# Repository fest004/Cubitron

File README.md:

```
   ▄█   ▄█▄ ███    █▄  ▀█████████▄     ▄████████ ███▄▄▄▄   
  ███ ▄███▀ ███    ███   ███    ███   ███    ███ ███▀▀▀██▄ 
  ███▐██▀   ███    ███   ███    ███   ███    █▀  ███   ███ 
 ▄█████▀    ███    ███  ▄███▄▄▄██▀   ▄███▄▄▄     ███   ███ 
▀▀█████▄    ███    ███ ▀▀███▀▀▀██▄  ▀▀███▀▀▀     ███   ███ 
  ███▐██▄   ███    ███   ███    ██▄   ███    █▄  ███   ███ 
  ███ ▀███▄ ███    ███   ███    ███   ███    ███ ███   ███ 
  ███   ▀█▀ ████████▀  ▄█████████▀    ██████████  ▀█   █▀  
  ▀                                                        
```
#### You can read about it here: [Link to documentation](https://fest004.github.io/Cubitron/)

#### Folder structure

```
.
├── docs             # Documents (datasheets, references, documentation)
├── hardware         # Hardware design files (CAD)
├── software         # Software files (source files, build files and binaries)
├── LICENSE
└── README.md
```

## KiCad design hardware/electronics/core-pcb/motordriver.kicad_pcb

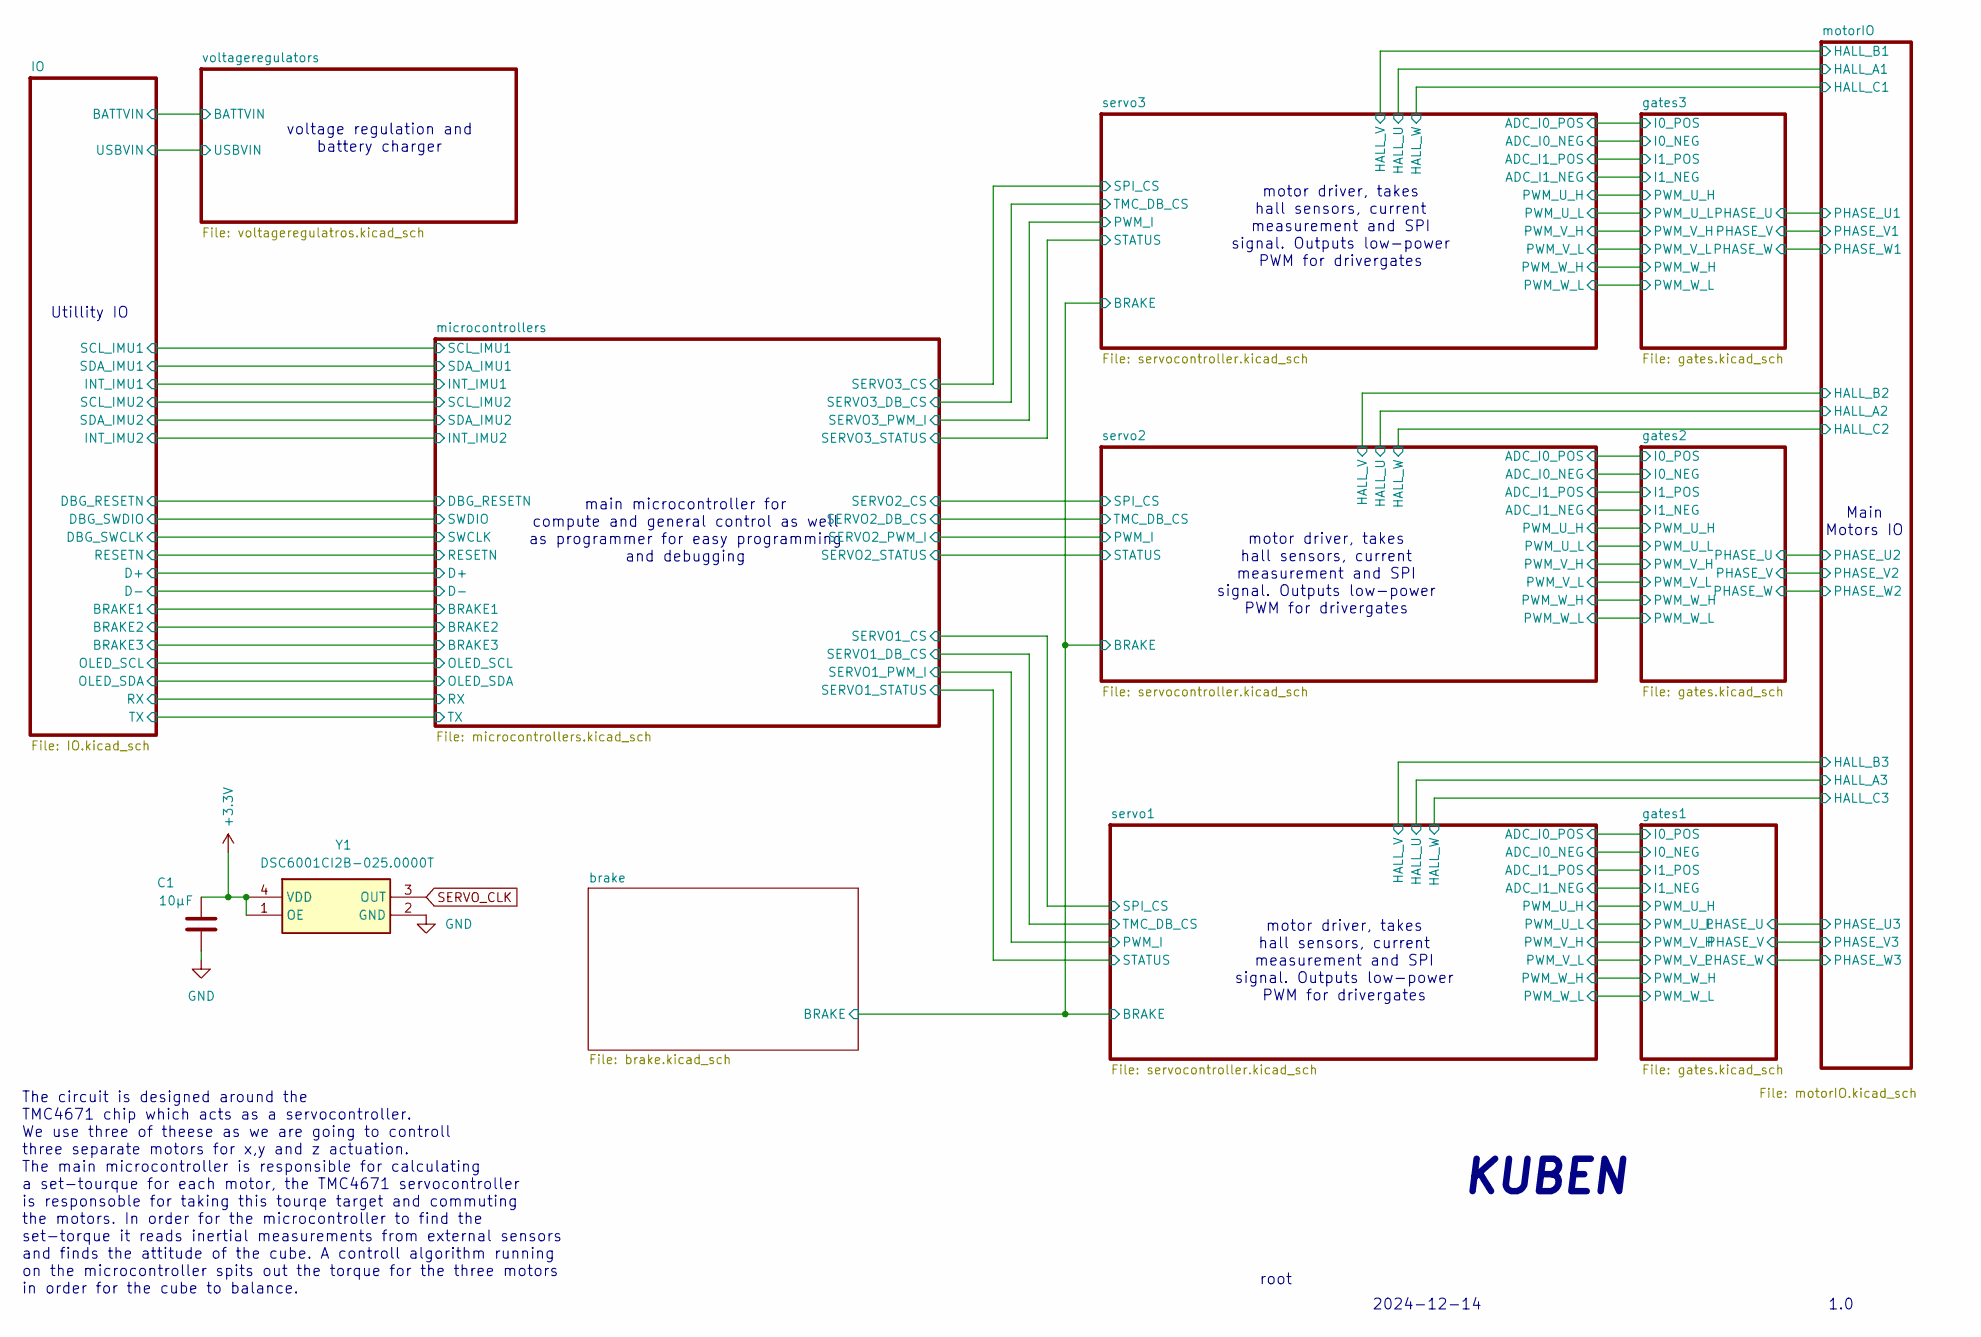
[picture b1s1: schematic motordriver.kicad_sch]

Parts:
C1: 10µF; C_0603_1608Metric
Y1: DSC6001CI2B-025.0000T; DSC6001CI2B0250000T; Mouser Part Number 579-1CI2B-025.0000T

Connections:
+3.3V: C1.1, Y1.1 (OE), Y1.4 (VDD); also elsewhere on the board
SERVO_CLK: Y1.3 (OUT); also elsewhere on the board

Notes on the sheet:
1.0
voltage regulation and battery charger
motor driver, takes hall sensors, current measurement and SPI signal. Outputs low-power PWM for drivergates
root
Main Motors IO
KUBEN
2024-12-14
main microcontroller for compute and general control as well as programmer for easy programming and debugging
Utillity IO
The circuit is designed around the TMC4671 chip which acts as a servocontroller. We use three of theese as we are going to controll three separate motors for x,y and z actuation. The main microcontroller is responsible for calculating a set-tourque for each motor, the TMC4671 servocontroller is res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

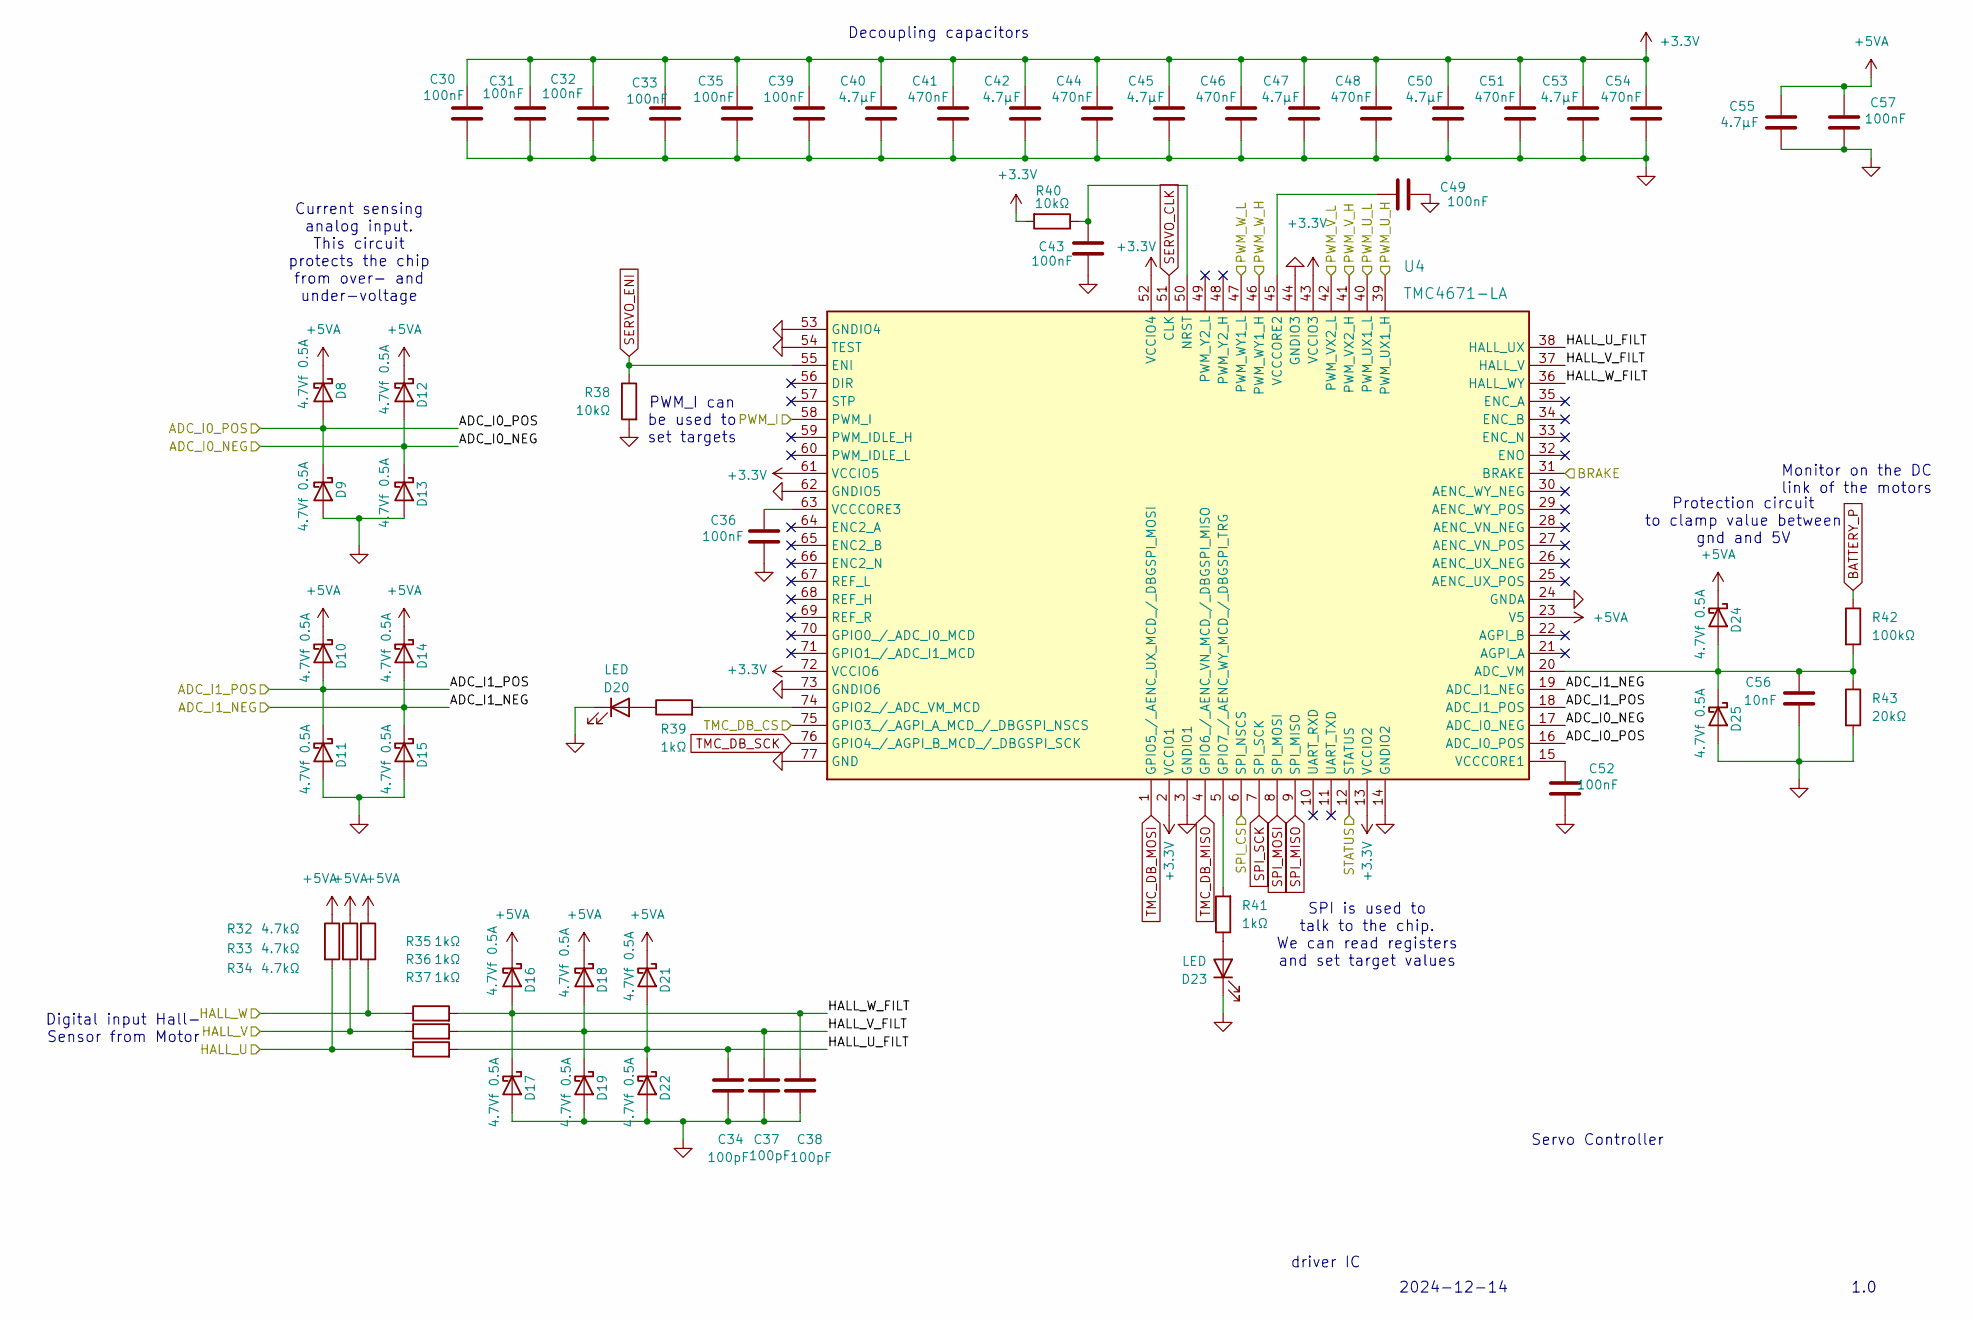
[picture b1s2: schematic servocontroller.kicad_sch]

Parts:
C30, C31, C32, C33, C35, C36, C39, C43, C49, C52, C57: 100nF; C_0603_1608Metric
C34, C37, C38: 100pF; C_0603_1608Metric
C40, C42, C45, C47, C50, C53, C55: 4.7µF; C_0603_1608Metric
C41, C44, C46, C48, C51, C54: 470nF; C_0603_1608Metric
C56: 10nF; C_0603_1608Metric
D8, D9, D10, D11, D12, D13, D14, D15, D16, D17, D18, D19, D21, D22, D24, D25: 4.7Vf 0.5A; DIOC1709X85N; Mouser Part Number 750-CDBU0520
D20, D23: LED; D_0603_1608Metric
R32, R33, R34: 4.7kΩ; R_0603_1608Metric
R35, R36, R37, R39, R41: 1kΩ; R_0603_1608Metric
R38, R40: 10kΩ; R_0603_1608Metric
R42: 100kΩ; R_0603_1608Metric
R43: 20kΩ; R_0603_1608Metric
U4: TMC4671-LA; QFN40P1050X650X90-77N; Mouser Part Number 700-TMC4671-LA

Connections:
+2.5V: D12.2 (A), D13.1 (K), D14.2 (A), D15.1 (K), U4.17 (ADC_I0_NEG), U4.19 (ADC_I1_NEG); also elsewhere on the board
+3.3V: C30.2, C31.2, C32.2, C33.2, C35.2, C39.2, C40.2, C41.2, C42.2, C44.2, C45.2, C46.2, C47.2, C48.2, C50.2, C51.2, C53.2, C54.2, R40.2, U4.2 (VCCIO1), U4.13 (VCCIO2), U4.43 (VCCIO3), U4.52 (VCCIO4), U4.61 (VCCIO5), U4.72 (VCCIO6); also elsewhere on the board
+5VA: C55.2, C57.2, D8.1 (K), D10.1 (K), D12.1 (K), D14.1 (K), D16.1 (K), D18.1 (K), D21.1 (K), D24.1 (K), R32.1, R33.1, R34.1, U4.23 (V5); also elsewhere on the board
/brake/BRAKE: U4.31 (BRAKE); also elsewhere on the board
/gates1/PWM_U_H: U4.39 (PWM_UX1_H); also elsewhere on the board
/gates1/PWM_U_L: U4.40 (PWM_UX1_L); also elsewhere on the board
/gates1/PWM_V_H: U4.41 (PWM_VX2_H); also elsewhere on the board
/gates1/PWM_V_L: U4.42 (PWM_VX2_L); also elsewhere on the board
/gates1/PWM_W_H: U4.46 (PWM_WY1_H); also elsewhere on the board
/gates1/PWM_W_L: U4.47 (PWM_WY1_L); also elsewhere on the board
/microcontrollers/SERVO1_CS: U4.6 (SPI_NSCS); also elsewhere on the board
/microcontrollers/SERVO1_DB_CS: U4.75 (GPIO3_/_AGPI_A_MCD_/_DBGSPI_NSCS); also elsewhere on the board
/microcontrollers/SERVO1_PWM_I: U4.58 (PWM_I); also elsewhere on the board
/microcontrollers/SERVO1_STATUS: U4.12 (STATUS); also elsewhere on the board
/motorIO/HALL_A3: R32.2, R37.1; also elsewhere on the board
/motorIO/HALL_B3: R33.2, R36.1; also elsewhere on the board
/motorIO/HALL_C3: R34.2, R35.1; also elsewhere on the board
/servo1/ADC_I0_POS: D8.2 (A), D9.1 (K), U4.16 (ADC_I0_POS); also elsewhere on the board
/servo1/ADC_I1_POS: D10.2 (A), D11.1 (K), U4.18 (ADC_I1_POS); also elsewhere on the board
/servo1/HALL_U_FILT: C34.2, D21.2 (A), D22.1 (K), R37.2, U4.38 (HALL_UX); also elsewhere on the board
/servo1/HALL_V_FILT: C37.2, D18.2 (A), D19.1 (K), R36.2, U4.37 (HALL_V); also elsewhere on the board
/servo1/HALL_W_FILT: C38.2, D16.2 (A), D17.1 (K), R35.2, U4.36 (HALL_WY); also elsewhere on the board
BATTERY_P: R42.1; also elsewhere on the board
unnamed 112: D20.2 (A), R39.1; also elsewhere on the board
unnamed: D23.2 (A), R41.1
unnamed: C56.2, D24.2 (A), D25.1 (K), R42.2, R43.1, U4.20 (ADC_VM)
unnamed 211: R39.2, U4.74 (GPIO2_/_ADC_VM_MCD); also elsewhere on the board
unnamed: R41.2, U4.5 (GPIO7_/_AENC_WY_MCD_/_DBGSPI_TRG)
unnamed: C43.1, R40.1, U4.50 (NRST)
unnamed: C52.2, U4.15 (VCCCORE1)
unnamed: C49.2, U4.45 (VCCCORE2)
unnamed 216: C36.2, U4.63 (VCCCORE3); also elsewhere on the board
SERVO_CLK: U4.51 (CLK); also elsewhere on the board
SERVO_ENI: R38.1, U4.55 (ENI); also elsewhere on the board
SPI_MISO: U4.9 (SPI_MISO); also elsewhere on the board
SPI_MOSI: U4.8 (SPI_MOSI); also elsewhere on the board
SPI_SCK: U4.7 (SPI_SCK); also elsewhere on the board
TMC_DB_MISO: U4.4 (GPIO6_/_AENC_VN_MCD_/_DBGSPI_MISO); also elsewhere on the board
TMC_DB_MOSI: U4.1 (GPIO5_/_AENC_UX_MCD_/_DBGSPI_MOSI); also elsewhere on the board
TMC_DB_SCK: U4.76 (GPIO4_/_AGPI_B_MCD_/_DBGSPI_SCK); also elsewhere on the board

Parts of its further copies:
C74, C75, C76, C77, C79, C80, C83, C87, C93, C96, C101, C111, C112, C113, C114, C116, C117, C120, C124, C130, C133, C138: 100nF; C_0603_1608Metric
C78, C81, C82, C115, C118, C119: 100pF; C_0603_1608Metric
C84, C86, C89, C91, C94, C97, C99, C121, C123, C126, C128, C131, C134, C136: 4.7µF; C_0603_1608Metric
C85, C88, C90, C92, C95, C98, C122, C125, C127, C129, C132, C135: 470nF; C_0603_1608Metric
C100, C137: 10nF; C_0603_1608Metric
D33, D34, D35, D36, D37, D38, D39, D40, D41, D42, D43, D44, D46, D47, D49, D50, D55, D56, D57, D58, D59, D60, D61, D62, D63, D64, D65, D66, D68, D69, D71, D72: 4.7Vf 0.5A; DIOC1709X85N; Mouser Part Number 750-CDBU0520
D45, D48, D67, D70: LED; D_0603_1608Metric
R52, R53, R54, R77, R78, R79: 4.7kΩ; R_0603_1608Metric
R55, R56, R57, R59, R61, R80, R81, R82, R84, R86: 1kΩ; R_0603_1608Metric
R58, R60, R83, R85: 10kΩ; R_0603_1608Metric
R62, R87: 100kΩ; R_0603_1608Metric
R63, R88: 20kΩ; R_0603_1608Metric
U6, U7: TMC4671-LA; QFN40P1050X650X90-77N; Mouser Part Number 700-TMC4671-LA

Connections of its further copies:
+2.5V: D37.2 (A), D38.1 (K), D39.2 (A), D40.1 (K), D59.2 (A), D60.1 (K), D61.2 (A), D62.1 (K), U6.17 (ADC_I0_NEG), U6.19 (ADC_I1_NEG), U7.17 (ADC_I0_NEG), U7.19 (ADC_I1_NEG); also elsewhere on the board
+3.3V: C74.2, C75.2, C76.2, C77.2, C79.2, C83.2, C84.2, C85.2, C86.2, C88.2, C89.2, C90.2, C91.2, C92.2, C94.2, C95.2, C97.2, C98.2, C111.2, C112.2, C113.2, C114.2, C116.2, C120.2, C121.2, C122.2, C123.2, C125.2, C126.2, C127.2, C128.2, C129.2, C131.2, C132.2, C134.2, C135.2, R60.2, R85.2, U6.2 (VCCIO1), U6.13 (VCCIO2), U6.43 (VCCIO3), U6.52 (VCCIO4), U6.61 (VCCIO5), U6.72 (VCCIO6), U7.2 (VCCIO1), U7.13 (VCCIO2), U7.43 (VCCIO3), U7.52 (VCCIO4), U7.61 (VCCIO5), U7.72 (VCCIO6); also elsewhere on the board
+5VA: C99.2, C101.2, C136.2, C138.2, D33.1 (K), D35.1 (K), D37.1 (K), D39.1 (K), D41.1 (K), D43.1 (K), D46.1 (K), D49.1 (K), D55.1 (K), D57.1 (K), D59.1 (K), D61.1 (K), D63.1 (K), D65.1 (K), D68.1 (K), D71.1 (K), R52.1, R53.1, R54.1, R77.1, R78.1, R79.1, U6.23 (V5), U7.23 (V5); also elsewhere on the board
/brake/BRAKE: U6.31 (BRAKE), U7.31 (BRAKE); also elsewhere on the board
/gates2/PWM_U_H: U6.39 (PWM_UX1_H); also elsewhere on the board
/gates2/PWM_U_L: U6.40 (PWM_UX1_L); also elsewhere on the board
/gates2/PWM_V_H: U6.41 (PWM_VX2_H); also elsewhere on the board
/gates2/PWM_V_L: U6.42 (PWM_VX2_L); also elsewhere on the board
/gates2/PWM_W_H: U6.46 (PWM_WY1_H); also elsewhere on the board
/gates2/PWM_W_L: U6.47 (PWM_WY1_L); also elsewhere on the board
/gates3/PWM_U_H: U7.39 (PWM_UX1_H); also elsewhere on the board
/gates3/PWM_U_L: U7.40 (PWM_UX1_L); also elsewhere on the board
/gates3/PWM_V_H: U7.41 (PWM_VX2_H); also elsewhere on the board
/gates3/PWM_V_L: U7.42 (PWM_VX2_L); also elsewhere on the board
/gates3/PWM_W_H: U7.46 (PWM_WY1_H); also elsewhere on the board
/gates3/PWM_W_L: U7.47 (PWM_WY1_L); also elsewhere on the board
/microcontrollers/SERVO2_CS: U6.6 (SPI_NSCS); also elsewhere on the board
/microcontrollers/SERVO2_DB_CS: U6.75 (GPIO3_/_AGPI_A_MCD_/_DBGSPI_NSCS); also elsewhere on the board
/microcontrollers/SERVO2_PWM_I: U6.58 (PWM_I); also elsewhere on the board
/microcontrollers/SERVO2_STATUS: U6.12 (STATUS); also elsewhere on the board
/microcontrollers/SERVO3_CS: U7.6 (SPI_NSCS); also elsewhere on the board
/microcontrollers/SERVO3_DB_CS: U7.75 (GPIO3_/_AGPI_A_MCD_/_DBGSPI_NSCS); also elsewhere on the board
/microcontrollers/SERVO3_PWM_I: U7.58 (PWM_I); also elsewhere on the board
/microcontrollers/SERVO3_STATUS: U7.12 (STATUS); also elsewhere on the board
/motorIO/HALL_A1: R77.2, R82.1; also elsewhere on the board
/motorIO/HALL_A2: R52.2, R57.1; also elsewhere on the board
/motorIO/HALL_B1: R78.2, R81.1; also elsewhere on the board
/motorIO/HALL_B2: R53.2, R56.1; also elsewhere on the board
/motorIO/HALL_C1: R79.2, R80.1; also elsewhere on the board
/motorIO/HALL_C2: R54.2, R55.1; also elsewhere on the board
/servo2/ADC_I0_POS: D33.2 (A), D34.1 (K), U6.16 (ADC_I0_POS); also elsewhere on the board
/servo2/ADC_I1_POS: D35.2 (A), D36.1 (K), U6.18 (ADC_I1_POS); also elsewhere on the board
/servo2/HALL_U_FILT: C78.2, D46.2 (A), D47.1 (K), R57.2, U6.38 (HALL_UX)
/servo2/HALL_V_FILT: C81.2, D43.2 (A), D44.1 (K), R56.2, U6.37 (HALL_V)
/servo2/HALL_W_FILT: C82.2, D41.2 (A), D42.1 (K), R55.2, U6.36 (HALL_WY)
/servo3/ADC_I0_POS: D55.2 (A), D56.1 (K), U7.16 (ADC_I0_POS); also elsewhere on the board
/servo3/ADC_I1_POS: D57.2 (A), D58.1 (K), U7.18 (ADC_I1_POS); also elsewhere on the board
/servo3/HALL_U_FILT: C115.2, D68.2 (A), D69.1 (K), R82.2, U7.38 (HALL_UX)
/servo3/HALL_V_FILT: C118.2, D65.2 (A), D66.1 (K), R81.2, U7.37 (HALL_V)
/servo3/HALL_W_FILT: C119.2, D63.2 (A), D64.1 (K), R80.2, U7.36 (HALL_WY)
BATTERY_P: R62.1, R87.1; also elsewhere on the board
unnamed: D45.2 (A), R59.1
unnamed: D48.2 (A), R61.1
unnamed: C100.2, D49.2 (A), D50.1 (K), R62.2, R63.1, U6.20 (ADC_VM)
unnamed: D67.2 (A), R84.1
unnamed: D70.2 (A), R86.1
unnamed: C137.2, D71.2 (A), D72.1 (K), R87.2, R88.1, U7.20 (ADC_VM)
unnamed: R59.2, U6.74 (GPIO2_/_ADC_VM_MCD)
unnamed: R61.2, U6.5 (GPIO7_/_AENC_WY_MCD_/_DBGSPI_TRG)
unnamed 221: C87.1, R60.1, U6.50 (NRST); also elsewhere on the board
unnamed: C96.2, U6.15 (VCCCORE1)
unnamed: C93.2, U6.45 (VCCCORE2)
unnamed: C80.2, U6.63 (VCCCORE3)
unnamed: R84.2, U7.74 (GPIO2_/_ADC_VM_MCD)
unnamed: R86.2, U7.5 (GPIO7_/_AENC_WY_MCD_/_DBGSPI_TRG)
unnamed: C124.1, R85.1, U7.50 (NRST)
unnamed: C133.2, U7.15 (VCCCORE1)
unnamed: C130.2, U7.45 (VCCCORE2)
unnamed: C117.2, U7.63 (VCCCORE3)
SERVO_CLK: U6.51 (CLK), U7.51 (CLK); also elsewhere on the board
SERVO_ENI: R58.1, R83.1, U6.55 (ENI), U7.55 (ENI); also elsewhere on the board
SPI_MISO: U6.9 (SPI_MISO), U7.9 (SPI_MISO); also elsewhere on the board
SPI_MOSI: U6.8 (SPI_MOSI), U7.8 (SPI_MOSI); also elsewhere on the board
SPI_SCK: U6.7 (SPI_SCK), U7.7 (SPI_SCK); also elsewhere on the board
TMC_DB_MISO: U6.4 (GPIO6_/_AENC_VN_MCD_/_DBGSPI_MISO), U7.4 (GPIO6_/_AENC_VN_MCD_/_DBGSPI_MISO); also elsewhere on the board
TMC_DB_MOSI: U6.1 (GPIO5_/_AENC_UX_MCD_/_DBGSPI_MOSI), U7.1 (GPIO5_/_AENC_UX_MCD_/_DBGSPI_MOSI); also elsewhere on the board
TMC_DB_SCK: U6.76 (GPIO4_/_AGPI_B_MCD_/_DBGSPI_SCK), U7.76 (GPIO4_/_AGPI_B_MCD_/_DBGSPI_SCK); also elsewhere on the board

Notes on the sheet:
Monitor on the DC link of the motors
Servo Controller
driver IC
Current sensing analog input. This circuit protects the chip from over- and under-voltage
Decoupling capacitors
2024-12-14
Protection circuit to clamp value between gnd and 5V
SPI is used to talk to the chip. We can read registers and set target values
1.0
PWM_I can be used to set targets
Digital input Hall- Sensor from Motor

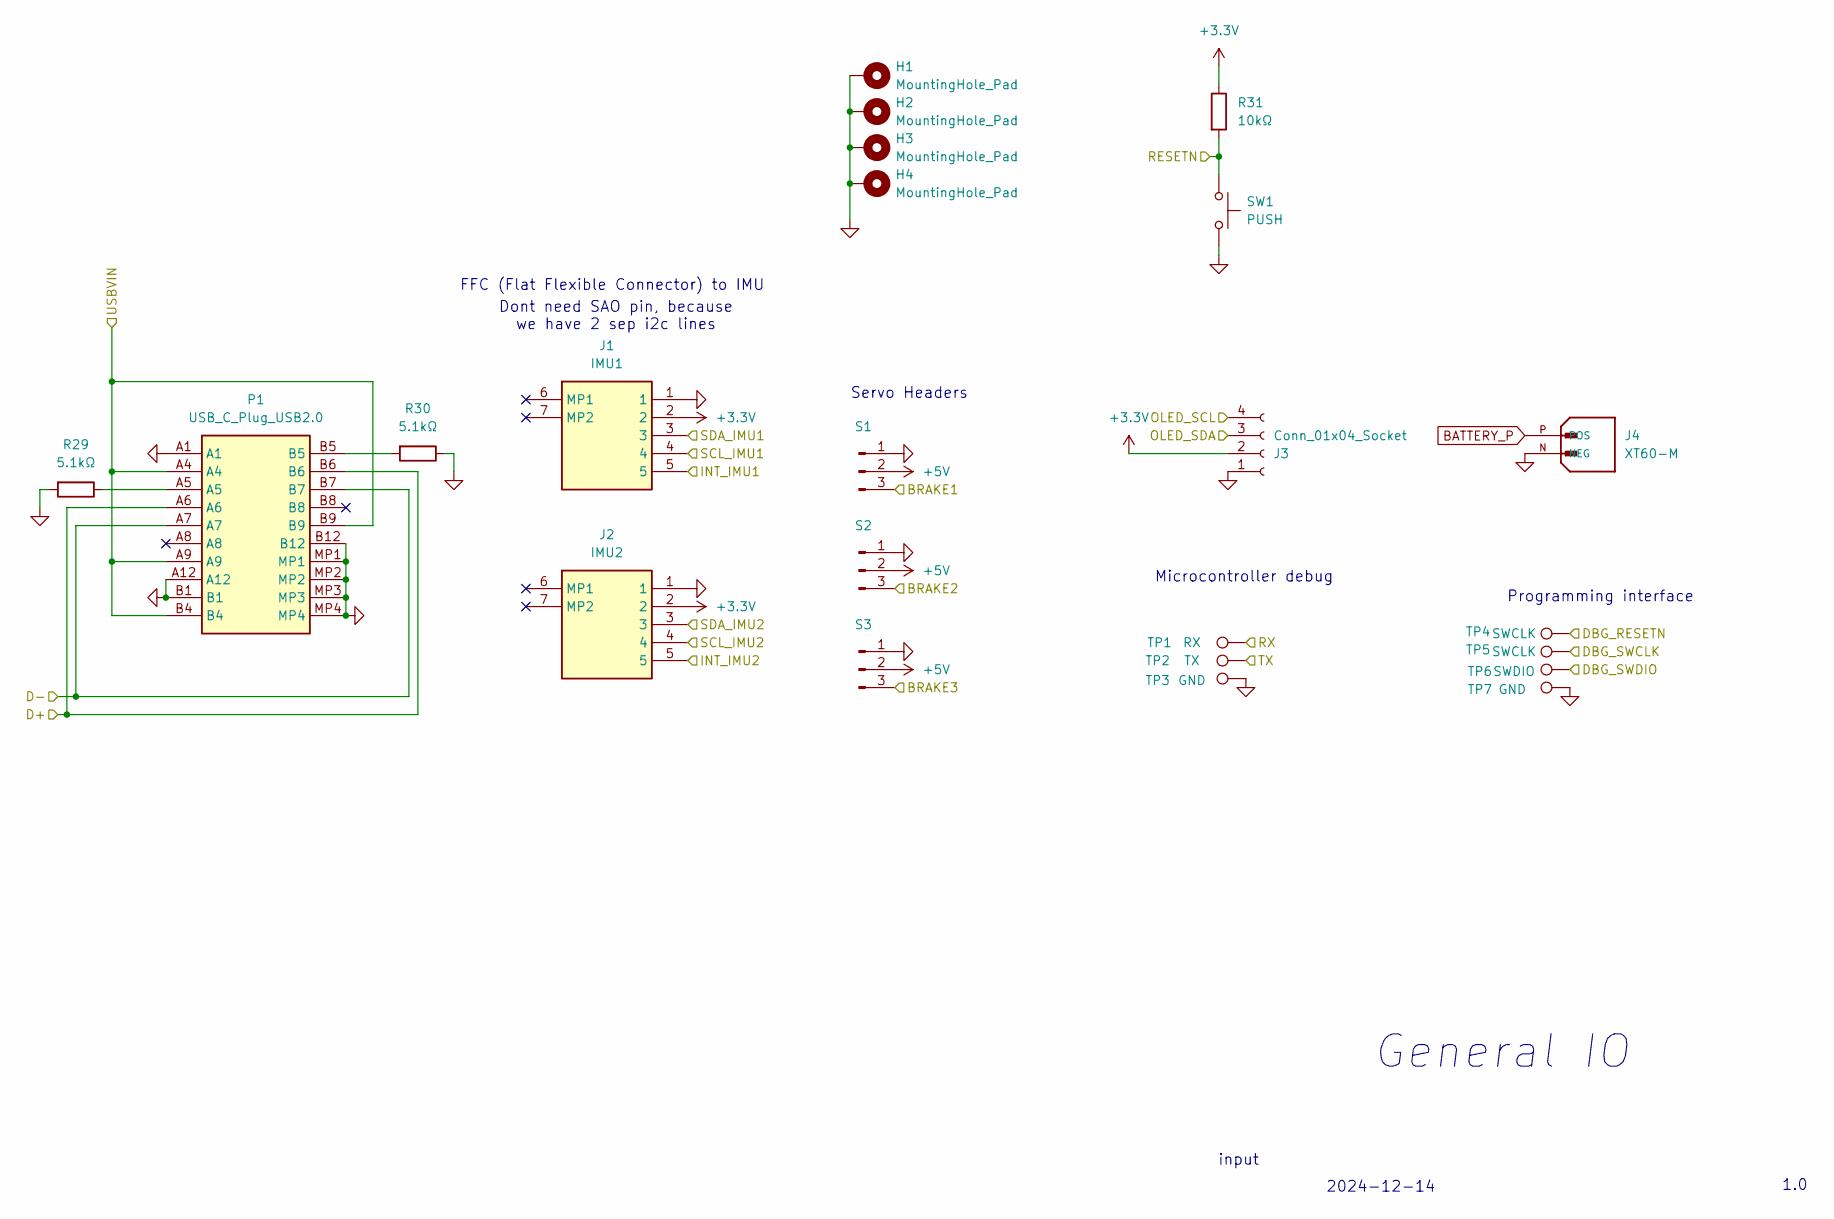
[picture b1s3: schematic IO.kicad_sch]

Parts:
H1, H2, H3, H4: MountingHole_Pad; MountingHole_3.2mm_M3_DIN965_Pad
J1: IMU1; 59453052110ECHLF; Manufacturer_Part_Number 59453-052110ECHLF
J2: IMU2; 59453052110ECHLF; Manufacturer_Part_Number 59453-052110ECHLF
J3: Conn_01x04_Socket; PinSocket_1x04_P2.54mm_Vertical
J4: XT60-M; AMASS_XT60-M; PARTREV V1.2
P1: USB_C_Plug_USB2.0; USB4110GFA; Mouser Part Number 640-USB4110-GF-A
R29, R30: 5.1kΩ; R_0603_1608Metric
R31: 10kΩ; R_0603_1608Metric
S1, S2, S3: PinHeader_1x03_P2.54mm_Vertical
SW1: PUSH; SW_PUSH_6mm
TP1: RX; TestPoint_Pad_D1.5mm
TP2: TX; TestPoint_Pad_D1.5mm
TP3, TP7: GND; TestPoint_Pad_D1.5mm
TP4, TP5: SWCLK; TestPoint_Pad_D1.5mm
TP6: SWDIO; TestPoint_Pad_D1.5mm

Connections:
+3.3V: J1.2, J2.2, J3.2, R31.1; also elsewhere on the board
+5V: S1.2, S2.2, S3.2
/IO/BRAKE1: S1.3; also elsewhere on the board
/IO/BRAKE2: S2.3; also elsewhere on the board
/IO/BRAKE3: S3.3; also elsewhere on the board
/IO/D+: P1.A6, P1.B6; also elsewhere on the board
/IO/D-: P1.A7, P1.B7; also elsewhere on the board
/IO/DBG_RESETN: TP4.1; also elsewhere on the board
/IO/DBG_SWCLK: TP5.1; also elsewhere on the board
/IO/DBG_SWDIO: TP6.1; also elsewhere on the board
/IO/INT_IMU1: J1.5; also elsewhere on the board
/IO/INT_IMU2: J2.5; also elsewhere on the board
/IO/OLED_SCL: J3.4; also elsewhere on the board
/IO/OLED_SDA: J3.3; also elsewhere on the board
/IO/RX: TP1.1; also elsewhere on the board
/IO/SCL_IMU1: J1.4; also elsewhere on the board
/IO/SCL_IMU2: J2.4; also elsewhere on the board
/IO/SDA_IMU1: J1.3; also elsewhere on the board
/IO/SDA_IMU2: J2.3; also elsewhere on the board
/IO/TX: TP2.1; also elsewhere on the board
/IO/USBVIN: P1.A4, P1.A9, P1.B4, P1.B9; also elsewhere on the board
/microcontrollers/RESETN: R31.2, SW1.1; also elsewhere on the board
BATTERY_P: J4.P (POS); also elsewhere on the board
unnamed: P1.A5, R29.1
unnamed 188: P1.B5, R30.2; also elsewhere on the board

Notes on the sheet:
input
Dont need SAO pin, because we have 2 sep i2c lines
General IO
FFC (Flat Flexible Connector) to IMU
Programming interface
Microcontroller debug
Servo Headers
2024-12-14
1.0

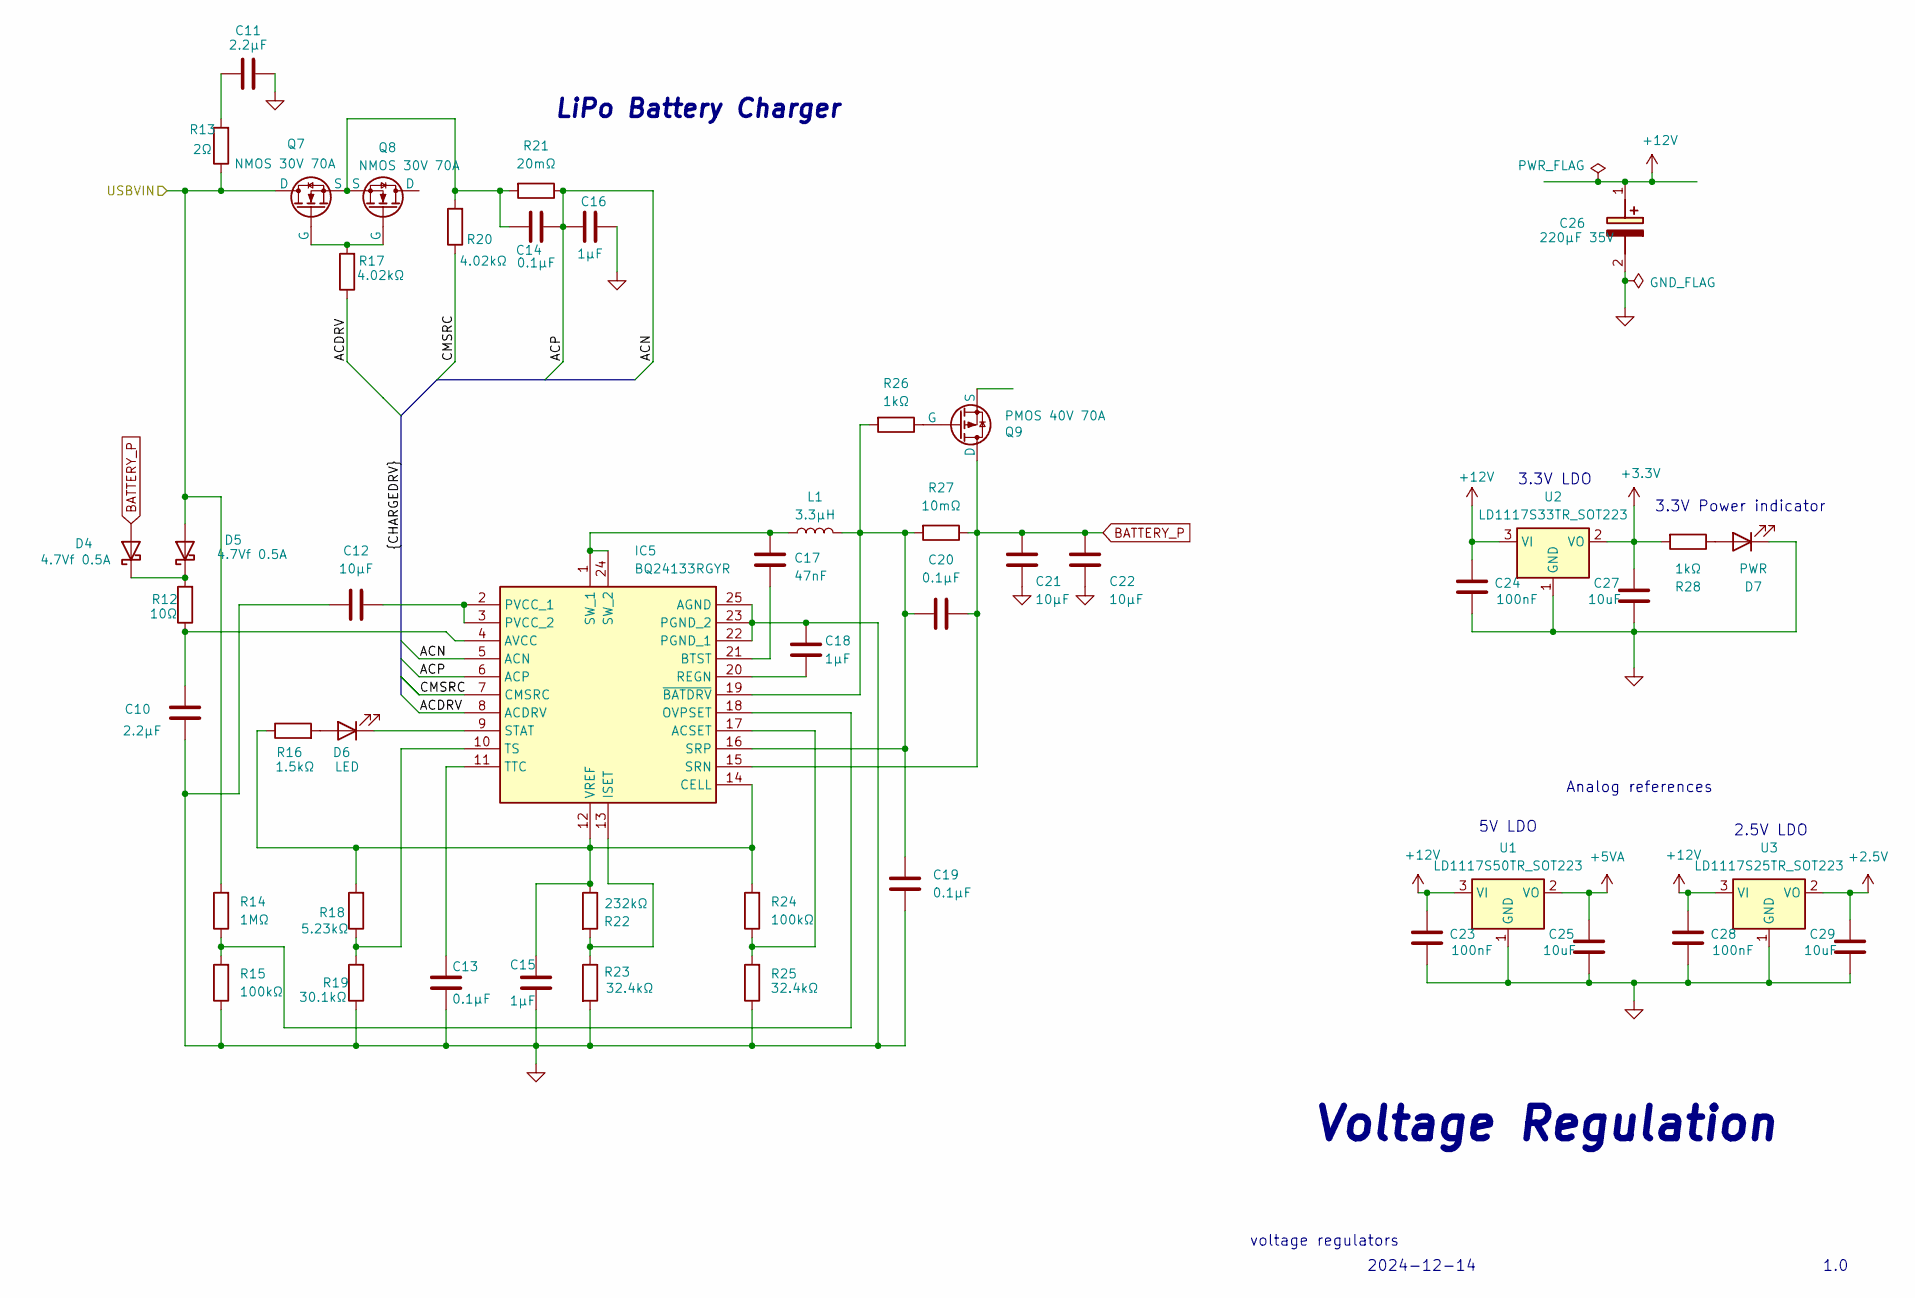
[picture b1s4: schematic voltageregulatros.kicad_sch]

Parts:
C10, C11: 2.2µF; C_0603_1608Metric
C12, C21, C22: 10µF; C_0603_1608Metric
C13, C14, C19, C20: 0.1µF; C_0603_1608Metric
C15, C16, C18: 1µF; C_0603_1608Metric
C17: 47nF; C_0603_1608Metric
C23, C24, C28: 100nF; C_0603_1608Metric
C25, C27, C29: 10uF; C_0603_1608Metric
C26: 220µF 35V; CAPAE1050X1050N; Mouser Part Number 594-MAL215099001E3
D4, D5: 4.7Vf 0.5A; DIOC1709X85N; Mouser Part Number 750-CDBU0520
D6: LED; D_0603_1608Metric
D7: PWR; D_0603_1608Metric
IC5: BQ24133RGYR; Mouser Part Number 595-BQ24133RGYR
L1: 3.3µH; INDPM6965X300N; Mouser Part Number 70-IHLP2525CZER3R3M0
Q7, Q8: NMOS 30V 70A; IPD047N03LF2SATMA1
Q9: PMOS 40V 70A; IPD70P04P4L08ATMA2
R12: 10Ω; R_0603_1608Metric
R13: 2Ω; R_0603_1608Metric
R14: 1MΩ; R_0603_1608Metric
R15, R24: 100kΩ; R_0603_1608Metric
R16: 1.5kΩ; R_0603_1608Metric
R17, R20: 4.02kΩ; R_0603_1608Metric
R18: 5.23kΩ; R_0603_1608Metric
R19: 30.1kΩ; R_0603_1608Metric
R21: 20mΩ; R_0603_1608Metric
R22: 232kΩ; R_0603_1608Metric
R23, R25: 32.4kΩ; R_0603_1608Metric
R26, R28: 1kΩ; R_0603_1608Metric
R27: 10mΩ; R_0603_1608Metric
U1: LD1117S50TR_SOT223; SOT-223-3_TabPin2
U2: LD1117S33TR_SOT223; SOT-223-3_TabPin2
U3: LD1117S25TR_SOT223; SOT-223-3_TabPin2

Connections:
+2.5V: C29.1, U3.2 (VO); also elsewhere on the board
+3.3V: C27.1, R28.2, U2.2 (VO); also elsewhere on the board
+5VA: C25.1, U1.2 (VO); also elsewhere on the board
+12V: C23.1, C24.1, C26.1 (+), C28.1, U1.3 (VI), U2.3 (VI), U3.3 (VI); also elsewhere on the board
/IO/USBVIN: D5.2 (A), Q7.1 (D), R13.1, R14.2; also elsewhere on the board
/voltageregulators/ACDRV: IC5.8 (ACDRV), R17.1
/voltageregulators/ACP: C14.2, C16.1, IC5.5 (ACN), IC5.6 (ACP), R21.1
/voltageregulators/CMSRC: IC5.7 (CMSRC), R20.1
BATTERY_P: C20.2, C21.1, C22.1, D4.2 (A), IC5.15 (SRN), Q9.2 (D), R27.1; also elsewhere on the board
unnamed: C11.1, R13.2
unnamed: D4.1 (K), D5.1 (K), R12.2
unnamed: D6.2 (A), R16.2
unnamed: D6.1 (K), IC5.9 (STAT)
unnamed 111: D7.2 (A), R28.1; also elsewhere on the board
unnamed: IC5.17 (ACSET), R24.1, R25.2
unnamed: C10.1, IC5.4 (AVCC), R12.1
unnamed: C17.1, IC5.21 (BTST)
unnamed: C15.1, IC5.12 (VREF), IC5.14 (CELL), R16.1, R18.2, R22.1, R24.2
unnamed: IC5.13 (ISET), R22.2, R23.1
unnamed: IC5.18 (OVPSET), R14.1, R15.2
unnamed: C18.1, IC5.20 (REGN)
unnamed: C19.2, C20.1, IC5.16 (SRP), IC5.19 (~BATDRV), L1.2, R26.2, R27.2
unnamed: C17.2, IC5.1 (SW_1), IC5.24 (SW_2), L1.1
unnamed: IC5.10 (TS), R18.1, R19.2
unnamed: C13.1, IC5.11 (TTC)
unnamed: Q7.2 (G), Q8.2 (G), R17.2
unnamed: C14.1, Q7.3 (S), Q8.3 (S), R20.2, R21.2
unnamed: Q9.1 (G), R26.1

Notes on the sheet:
Analog references
1.0
3.3V Power indicator
2024-12-14
2.5V LDO
Voltage Regulation
LiPo Battery Charger
5V LDO
voltage regulators
3.3V LDO
